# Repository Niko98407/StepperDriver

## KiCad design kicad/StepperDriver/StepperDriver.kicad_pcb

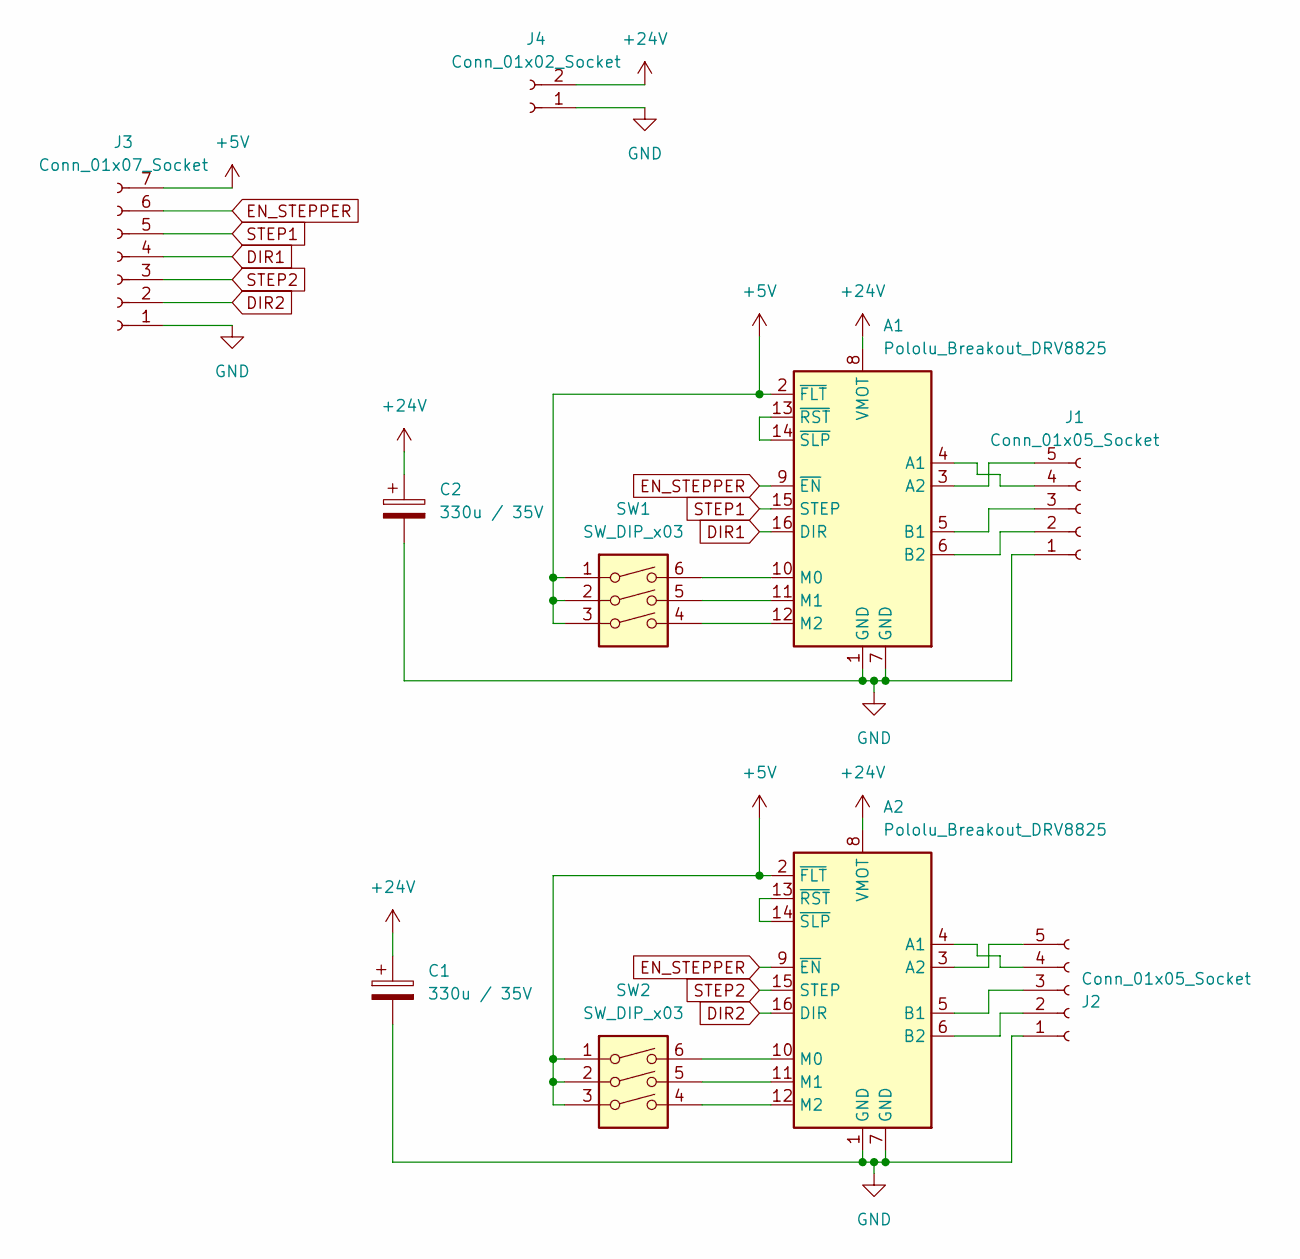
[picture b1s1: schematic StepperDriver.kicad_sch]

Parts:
A1, A2: Pololu_Breakout_DRV8825; Pololu_Breakout-16_15.2x20.3mm
C1, C2: 330u / 35V; CP_Elec_10x7.9
J1, J2: Conn_01x05_Socket; TerminalBlock_RND_205-00004_1x05_P5.00mm_Horizontal
J3: Conn_01x07_Socket; TerminalBlock_RND_205-00006_1x07_P5.00mm_Horizontal
J4: Conn_01x02_Socket; TerminalBlock_RND_205-00001_1x02_P5.00mm_Horizontal
SW1, SW2: SW_DIP_x03; DIP-6_W7.62mm_Socket_LongPads

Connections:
+5V: A1.2 (~FLT), A2.2 (~FLT), J3.7, SW1.1, SW1.2, SW1.3, SW2.1, SW2.2, SW2.3
+24V: A1.8 (VMOT), A2.8 (VMOT), C1.1, C2.1, J4.2
DIR1: A1.16 (DIR), J3.4
DIR2: A2.16 (DIR), J3.2
EN_STEPPER: A1.9 (~EN), A2.9 (~EN), J3.6
GND: A1.1 (GND), A1.7 (GND), A2.1 (GND), A2.7 (GND), C1.2, C2.2, J1.1, J2.1, J3.1, J4.1
unnamed: A1.4 (A1), J1.4
unnamed: A1.3 (A2), J1.5
unnamed: A1.5 (B1), J1.3
unnamed: A1.6 (B2), J1.2
unnamed: A1.10 (M0), SW1.6
unnamed: A1.11 (M1), SW1.5
unnamed: A1.12 (M2), SW1.4
unnamed: A1.13 (~RST), A1.14 (~SLP)
unnamed: A2.4 (A1), J2.4
unnamed: A2.3 (A2), J2.5
unnamed: A2.5 (B1), J2.3
unnamed: A2.6 (B2), J2.2
unnamed: A2.10 (M0), SW2.6
unnamed: A2.11 (M1), SW2.5
unnamed: A2.12 (M2), SW2.4
unnamed: A2.13 (~RST), A2.14 (~SLP)
STEP1: A1.15 (STEP), J3.5
STEP2: A2.15 (STEP), J3.3

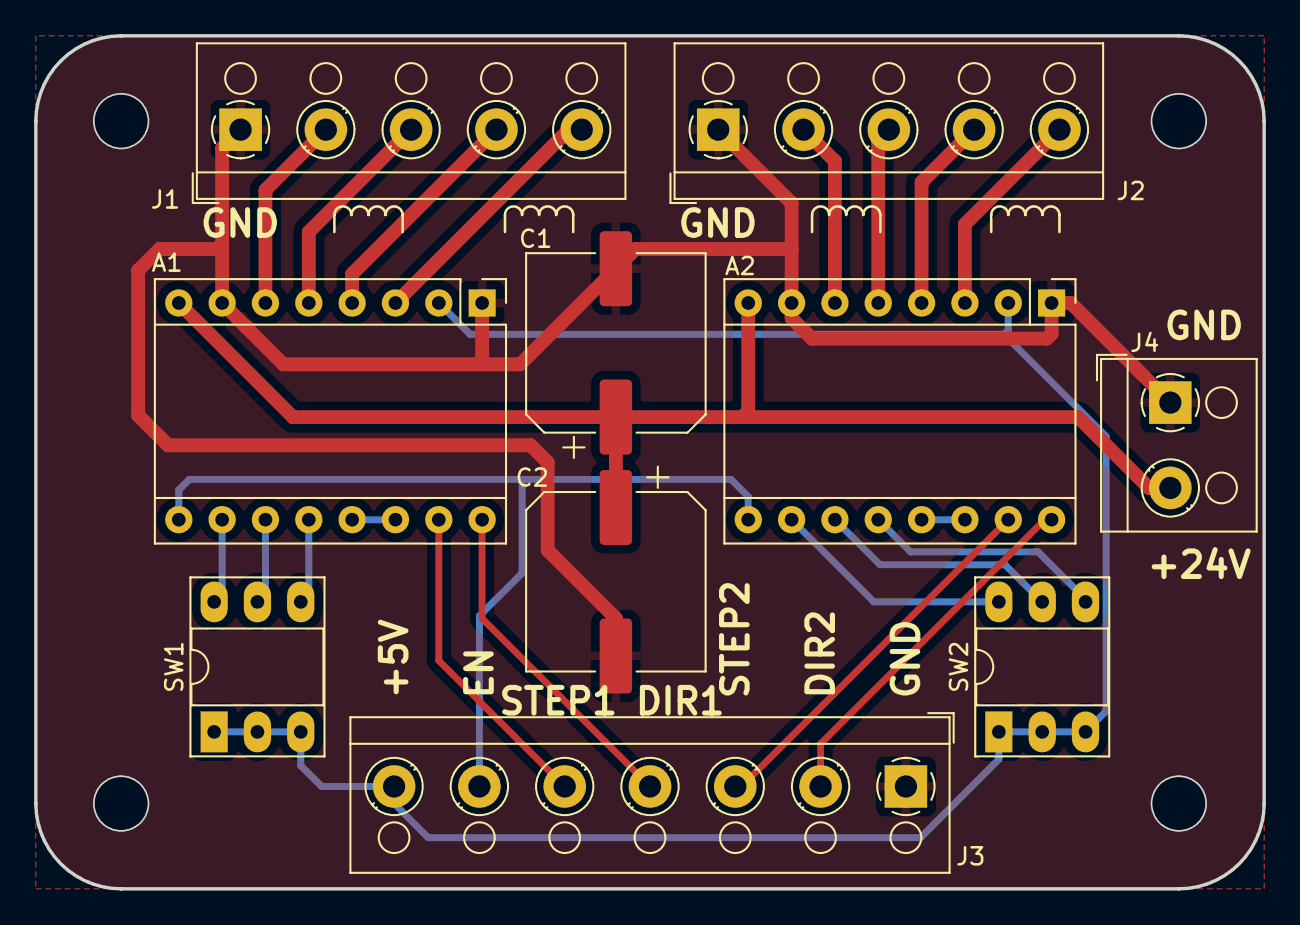
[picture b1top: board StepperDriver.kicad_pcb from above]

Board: 2 copper layers, 72.0 x 50.0 mm, 10 parts (0 on the bottom side), 24 nets.

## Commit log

2024-04-12 add project
